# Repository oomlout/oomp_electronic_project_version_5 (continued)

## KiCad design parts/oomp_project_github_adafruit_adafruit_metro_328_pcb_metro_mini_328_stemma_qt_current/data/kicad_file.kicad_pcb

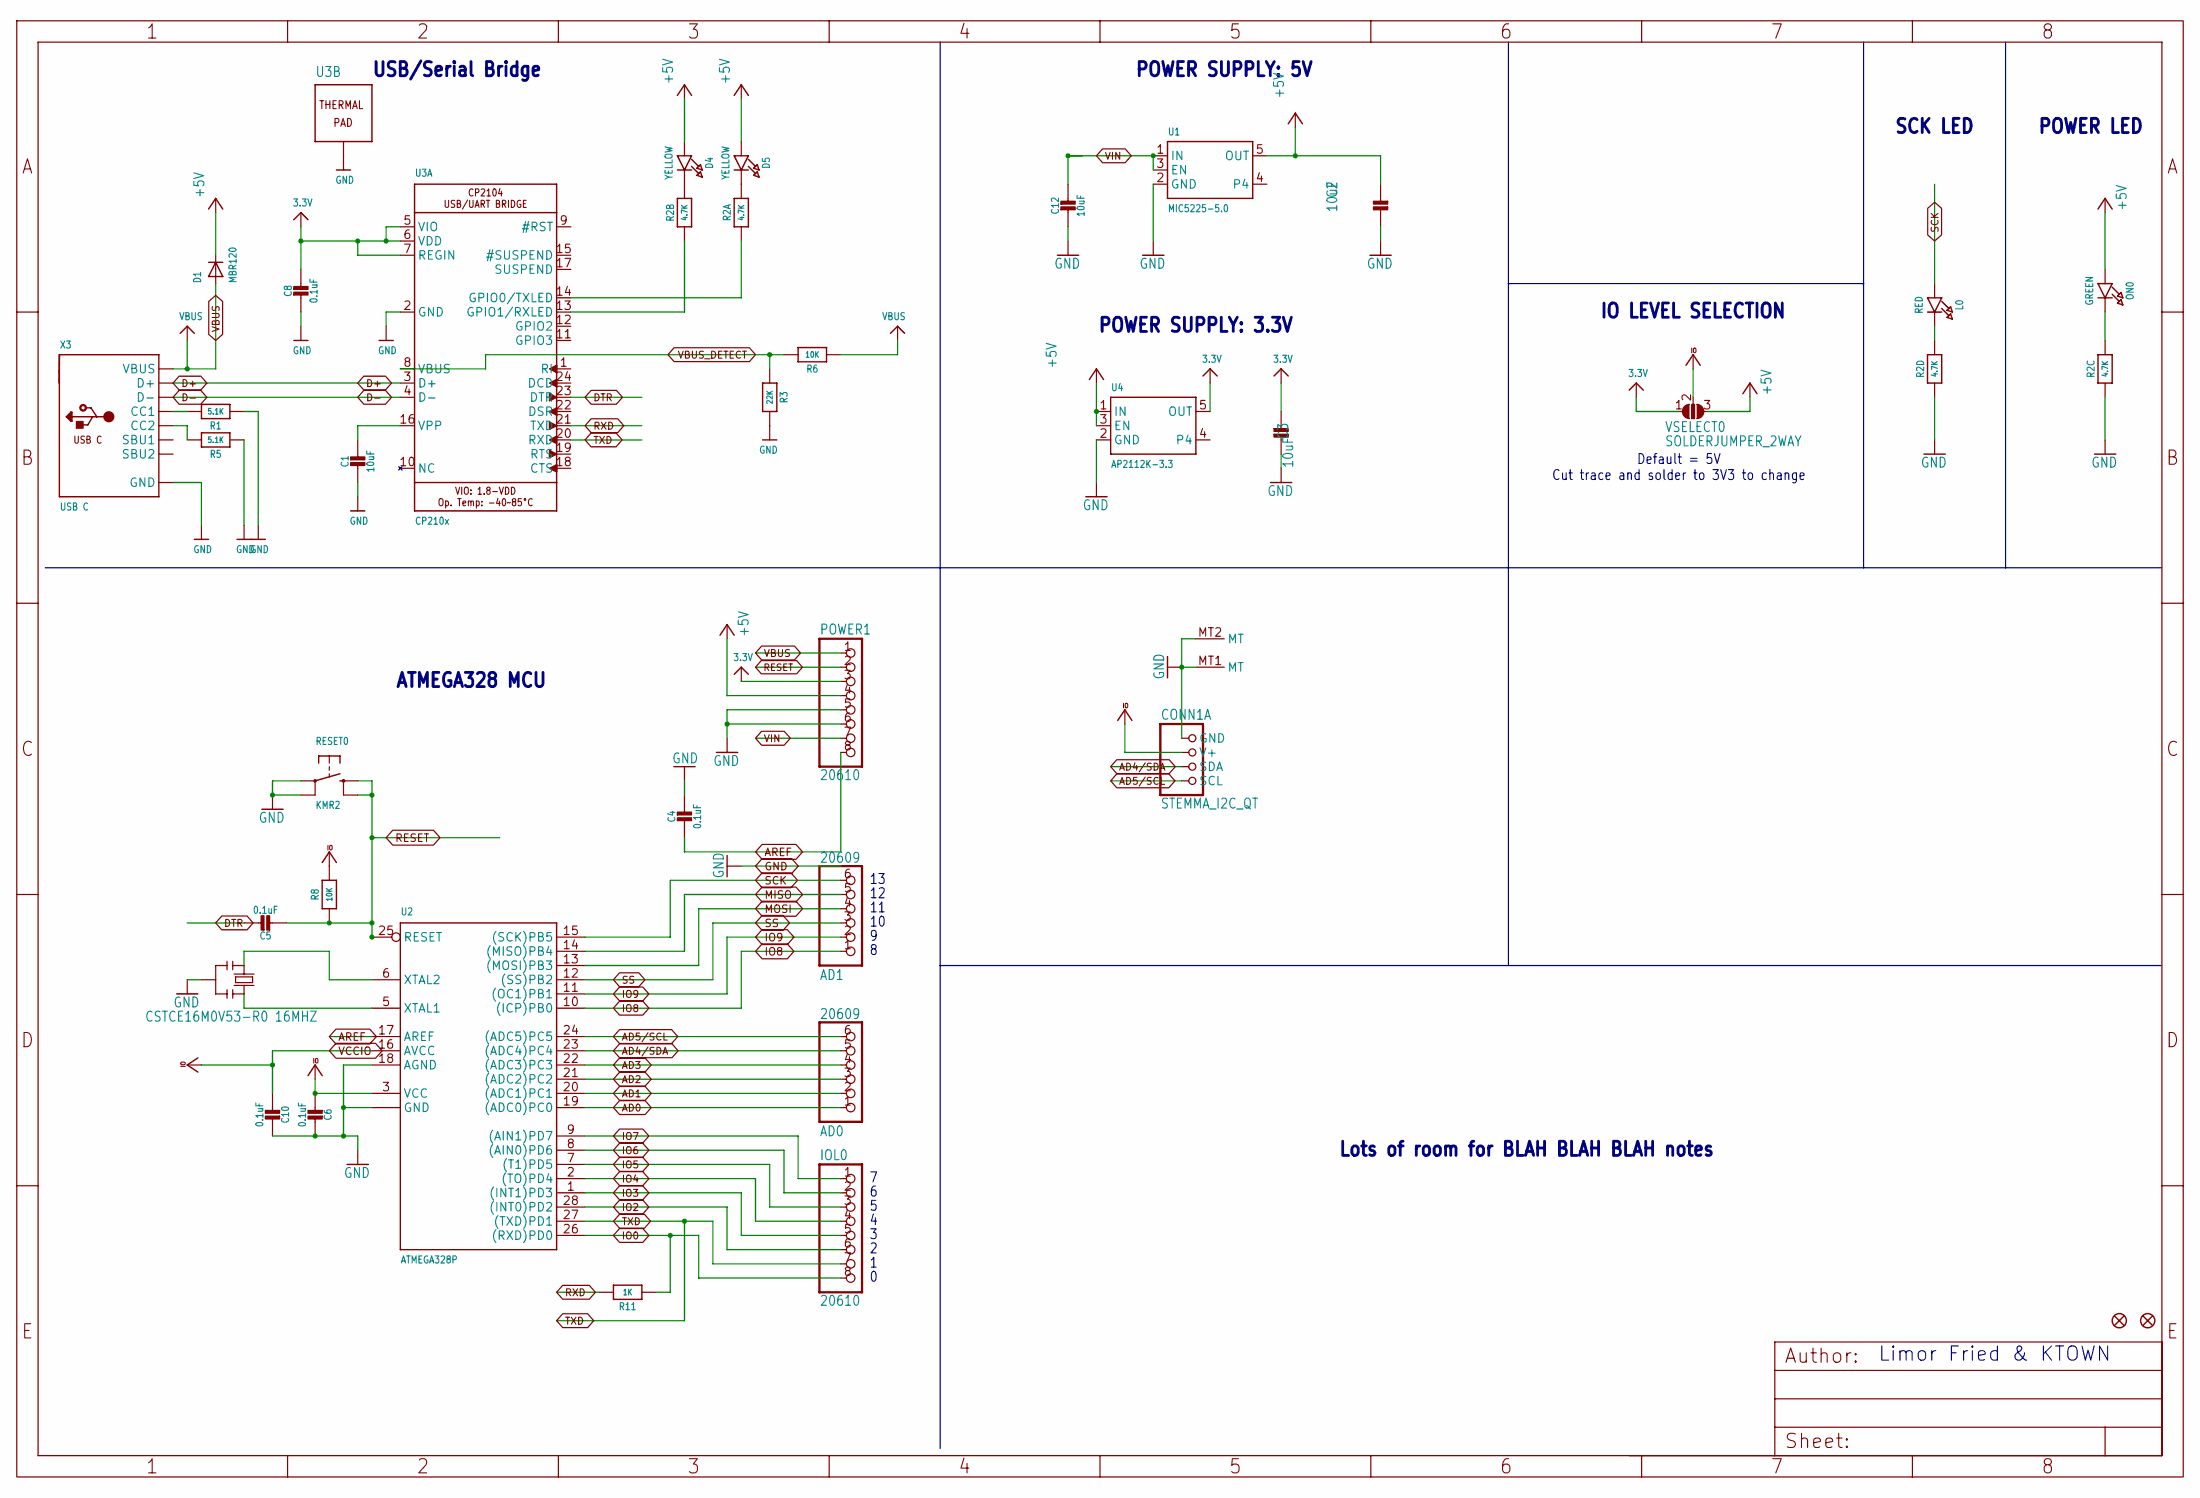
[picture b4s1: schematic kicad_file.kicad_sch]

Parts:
AD0, AD1: 20609; 1X06_ROUND
C1, C2, C3, C12: 10uF; 0805-NO
C4, C5, C6, C8, C10: 0.1uF; 0603-NO
CONN1: STEMMA_I2C_QT; JST_SH4
D1: MBR120; SOD-123FL
D4, D5: YELLOW; CHIPLED_0603_NOOUTLINE
FD1, FD2: FIDUCIAL_1MM
IOL0: 20610; 1X08_ROUND
L0: RED; CHIPLED_0603_NOOUTLINE
ON0: GREEN; CHIPLED_0603_NOOUTLINE
POWER1: 20610; 1X08_ROUND_70
R1, R5: 5.1K; 0603-NO
R2: 4.7K; RESPACK_4X0603
R3: 22K; 0603-NO
R6, R8: 10K; 0603-NO
R11: 1K; 0603-NO
RESET0: KMR2; BTN_KMR2_4.6X2.8
U1: MIC5225-5.0; SOT23-5
U2: ATMEGA328P; QFN28_4MM_.45MM
U3: CP210x; QFN24_4MM_SMSC
U4: AP2112K-3.3; SOT23-5
VSELECT0: SOLDERJUMPER_2WAY; SOLDERJUMPER_2WAY_OPEN_NOPASTE
X3: USB C; USB_C_CUSB31-CFM2AX-01-X
Y2: CSTCE16M0V53-R0 16MHZ; RESONATOR

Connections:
3.3V: C3.2, C8.1, POWER1.3, U3.5 (VIO), U3.6 (VDD), U3.7 (REGIN), U4.5 (OUT), VSELECT0.1
+5V: C2.2, D1.C, D4.A, D5.A, ON0.A, POWER1.4, U1.5 (OUT), U4.1 (IN), U4.3 (EN), VSELECT0.3
AD0: AD0.1, U2.19 ((ADC0)PC0)
AD1: AD0.2, U2.20 ((ADC1)PC1)
AD2: AD0.3, U2.21 ((ADC2)PC2)
AD3: AD0.4, U2.22 ((ADC3)PC3)
AD4/SDA: AD0.5, CONN1.3 (SDA), U2.23 ((ADC4)PC4)
AD5/SCL: AD0.6, CONN1.4 (SCL), U2.24 ((ADC5)PC5)
AREF: C4.2, POWER1.8, U2.17 (AREF)
D+: U3.3 (D+), X3.A6 (D+), X3.B6 (D+)
D-: U3.4 (D-), X3.A7 (D-), X3.B7 (D-)
DTR: C5.1, U3.23 (DTR)
GND: C1.2, C2.1, C3.1, C4.1, C6.1, C8.2, C10.1, C12.2, CONN1.1 (GND), CONN1.MT1 (MT), CONN1.MT2 (MT), POWER1.5, POWER1.6, R1.1, R2.3 (1), R2.4 (1), R3.1, R5.1, RESET0.A, RESET0.A' (P1), U1.2 (GND), U2.4 (GND), U2.18 (AGND), U2.29 (GND), U3.2 (GND), U3.THERM (TP), U4.2 (GND), X3.A1B12 (GND), X3.B1A12 (GND), Y2.2
IO0: IOL0.8, R11.1, U2.26 ((RXD)PD0)
IO2: IOL0.6, U2.28 ((INT0)PD2)
IO3: IOL0.5, U2.1 ((INT1)PD3)
IO4: IOL0.4, U2.2 ((TO)PD4)
IO5: IOL0.3, U2.7 ((T1)PD5)
IO6: IOL0.2, U2.8 ((AIN0)PD6)
IO7: IOL0.1, U2.9 ((AIN1)PD7)
IO8: AD1.1, U2.10 ((ICP)PB0)
IO9: AD1.2, U2.11 ((OC1)PB1)
MISO: AD1.5, U2.14 ((MISO)PB4)
MOSI: AD1.4, U2.13 ((MOSI)PB3)
unnamed: L0.C, R2.5 (2)
unnamed: ON0.C, R2.6 (2)
unnamed: R2.1, U3.14 (GPIO0/TXLED)
unnamed: R1.2, X3.A5 (CC1)
unnamed: D4.C, R2.7 (2)
unnamed: D5.C, R2.8 (2)
unnamed: R5.2, X3.B5 (CC2)
unnamed: C1.1, U3.16 (VPP)
unnamed: R2.2 (1), U3.13 (GPIO1/RXLED)
RESET: C5.2, POWER1.2, R8.1, RESET0.B (S), RESET0.B' (S1), U2.25 (RESET)
RXD: R11.2, U3.21 (TXD)
SCK: AD1.6, L0.A, U2.15 ((SCK)PB5)
SS: AD1.3, U2.12 ((SS)PB2)
TXD: IOL0.7, U2.27 ((TXD)PD1), U3.20 (RXD)
VBUS: D1.A, POWER1.1, R6.2, X3.A4B9 (VBUS), X3.B4A9 (VBUS)
VBUS_DETECT: R3.2, R6.1, U3.8 (VBUS)
VCCIO: C6.2, C10.2, CONN1.2 (V+), R8.2, U2.3 (VCC), U2.16 (AVCC), VSELECT0.2
VIN: C12.1, POWER1.7, U1.1 (IN), U1.3 (EN)
XTAL1: U2.5 (XTAL1), Y2.3
XTAL2: U2.6 (XTAL2), Y2.1

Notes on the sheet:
POWER SUPPLY: 5V
SCK LED
POWER LED
Lots of room for BLAH BLAH BLAH notes
Limor Fried & KTOWN
Default = 5V Cut trace and solder to 3V3 to change
USB/Serial Bridge
IO LEVEL SELECTION
ATMEGA328 MCU
POWER SUPPLY: 3.3V

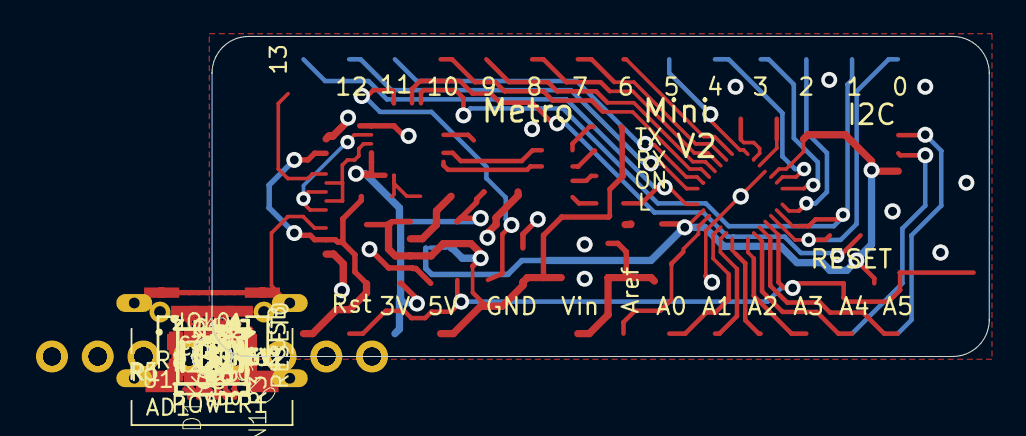
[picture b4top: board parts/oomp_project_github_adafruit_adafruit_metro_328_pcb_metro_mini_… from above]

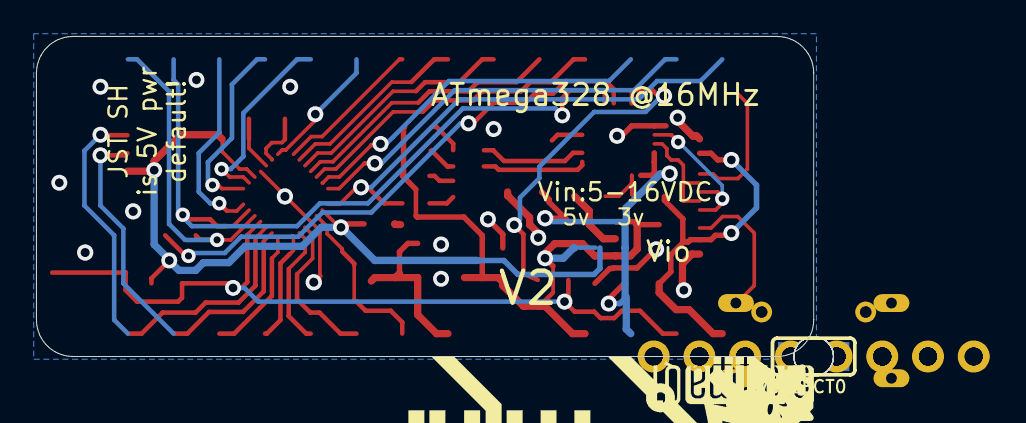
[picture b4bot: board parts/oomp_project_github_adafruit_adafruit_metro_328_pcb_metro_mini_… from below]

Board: 2 copper layers, 43.2 x 17.8 mm, 45 parts (4 on the bottom side), 44 nets.

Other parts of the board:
U$4: PCBFEAT-REV-040
U$5: ADAFRUIT_2.5MM
U$6: STEMMAQT
U$7: METROMINI_SILK
U$10: ADAFRUIT_5MM
UNK_HOLE_0: dummyfp0
UNK_HOLE_1: dummyfp1
UNK_HOLE_2: dummyfp2
UNK_HOLE_3: dummyfp3

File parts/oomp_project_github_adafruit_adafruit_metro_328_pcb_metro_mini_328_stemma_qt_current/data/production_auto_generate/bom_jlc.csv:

Comment,Designator,Footprint,LCSC Part #
,U$5,Metro Mini 328 V2 - STEMMA QT-import-fps:ADAFRUIT_2.5MM,
,U$10,Metro Mini 328 V2 - STEMMA QT-import-fps:ADAFRUIT_5MM,
,U$7,Metro Mini 328 V2 - STEMMA QT-import-fps:METROMINI_SILK,
,U$4,Metro Mini 328 V2 - STEMMA QT-import-fps:PCBFEAT-REV-040,
,VSELECT0,Metro Mini 328 V2 - STEMMA QT-import-fps:SOLDERJUMPER_2WAY_OPEN_NOPASTE,
,U$6,Metro Mini 328 V2 - STEMMA QT-import-fps:STEMMAQT,
0.1uF,"C4,C5,C6,C8,C10",Metro Mini 328 V2 - STEMMA QT-import-fps:0603-NO,C14663
10K,"R6,R8",Metro Mini 328 V2 - STEMMA QT-import-fps:0603-NO,C98220
10uF,"C1,C2,C3,C12",Metro Mini 328 V2 - STEMMA QT-import-fps:0805-NO,
1K,R11,Metro Mini 328 V2 - STEMMA QT-import-fps:0603-NO,C2907002
20609,"AD0,AD1",Metro Mini 328 V2 - STEMMA QT-import-fps:1X06_ROUND,C37208
20610,IOL0,Metro Mini 328 V2 - STEMMA QT-import-fps:1X08_ROUND,C492421
20610,POWER1,Metro Mini 328 V2 - STEMMA QT-import-fps:1X08_ROUND_70,C492421
22K,R3,Metro Mini 328 V2 - STEMMA QT-import-fps:0603-NO,C31850
4.7K,R2,Metro Mini 328 V2 - STEMMA QT-import-fps:RESPACK_4X0603,C23162
5.1K,"R1,R5",Metro Mini 328 V2 - STEMMA QT-import-fps:0603-NO,C23186
AP2112K-3.3,U4,Metro Mini 328 V2 - STEMMA QT-import-fps:SOT23-5,
ATMEGA328P,U2,Metro Mini 328 V2 - STEMMA QT-import-fps:QFN28_4MM_.45MM,
CP210x,U3,Metro Mini 328 V2 - STEMMA QT-import-fps:QFN24_4MM_SMSC,
CSTCE16M0V53-R0 16MHZ,Y2,Metro Mini 328 V2 - STEMMA QT-import-fps:RESONATOR,
FIDUCIAL_1MM,"FD1,FD2",Metro Mini 328 V2 - STEMMA QT-import-fps:FIDUCIAL_1MM,
GREEN,ON0,Metro Mini 328 V2 - STEMMA QT-import-fps:CHIPLED_0603_NOOUTLINE,
KMR2,RESET0,Metro Mini 328 V2 - STEMMA QT-import-fps:BTN_KMR2_4.6X2.8,
MBR120,D1,Metro Mini 328 V2 - STEMMA QT-import-fps:SOD-123FL,
MIC5225-5.0,U1,Metro Mini 328 V2 - STEMMA QT-import-fps:SOT23-5,
RED,L0,Metro Mini 328 V2 - STEMMA QT-import-fps:CHIPLED_0603_NOOUTLINE,
STEMMA_I2C_QT,CONN1,Metro Mini 328 V2 - STEMMA QT-import-fps:JST_SH4,C160404
USB C,X3,Metro Mini 328 V2 - STEMMA QT-import-fps:USB_C_CUSB31-CFM2AX-01-X,
YELLOW,"D4,D5",Metro Mini 328 V2 - STEMMA QT-import-fps:CHIPLED_0603_NOOUTLINE,

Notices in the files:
parts/oomp_project_github_adafruit_adafruit_menta_pcb_menta_current/data/original/kicad_file.kicad_sch:
Creative Commons 2.5
parts and their libraries:
COPYRIGHT: Copyright (C) 2018 Accelerated Designs. All rights reserved
